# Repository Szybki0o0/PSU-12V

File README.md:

# Dual Power Supply Circuit

## Overview
This schematic represents a **dual power supply circuit** that converts **12V AC** input into **regulated ±12V DC output**. It uses **linear voltage regulators (7812 and 7912)** to provide stable positive and negative 12V outputs.

## Main Components
1. **Power Input:**
   - **J1 (Barrel Jack Connector)**: Accepts **12V AC** input.
   - **D1, D2 (1N4007 Diodes)**: Forms a **bridge rectifier** for AC-to-DC conversion.

2. **Filtering Section:**
   - **C1, C2, C3, C4, C5, C6 (4700µF capacitors)**: Large **electrolytic capacitors** used for smoothing rectified DC voltage.
   - **C7, C8, C9, C10 (1µF capacitors)**: Additional filtering for improved stability.

3. **Voltage Regulators:**
   - **U1 (7812 Voltage Regulator)**: Provides a regulated **+12V DC output**.
   - **U2 (7912 Voltage Regulator)**: Provides a regulated **-12V DC output**.

4. **Protection Components:**
   - **D3 (1N4007 Diode)**: Protection diode to prevent reverse polarity damage.

## How It Works
1. **AC to DC Conversion**  
   - The **12V AC input** is rectified using **D1 and D2**, converting AC voltage to **pulsating DC**.
   - The **large electrolytic capacitors (C1-C6)** smooth the voltage to **reduce ripple**.

2. **Voltage Regulation**  
   - The **7812 regulator (U1)** outputs a steady **+12V DC**.
   - The **7912 regulator (U2)** outputs a steady **-12V DC**.
   - Small capacitors (C7-C10) help improve transient response and further reduce noise.

3. **Output**  
   - The final output at the **VoltageOut** terminal provides **+12V, GND, and -12V**, suitable for powering **operational amplifiers, audio circuits, and other dual-supply electronics**.

## Psysical implementation
Project has't been implemented on PCB but tested on a breadboard.

## Possible Improvements
- Adding **heat sinks** to the **7812 and 7912** for better thermal management. (It's mandatory)
- Using **fast-recovery diodes (e.g., UF4007)** instead of **1N4007** to improve efficiency.
- Implementing a **fuse** at the input for added protection.

## Applications
- **Operational amplifier circuits**
- **Audio amplifier power supplies**
- **Analog signal processing systems**
- **Dual-rail power supply requirements**

## Author
Jakub Konior

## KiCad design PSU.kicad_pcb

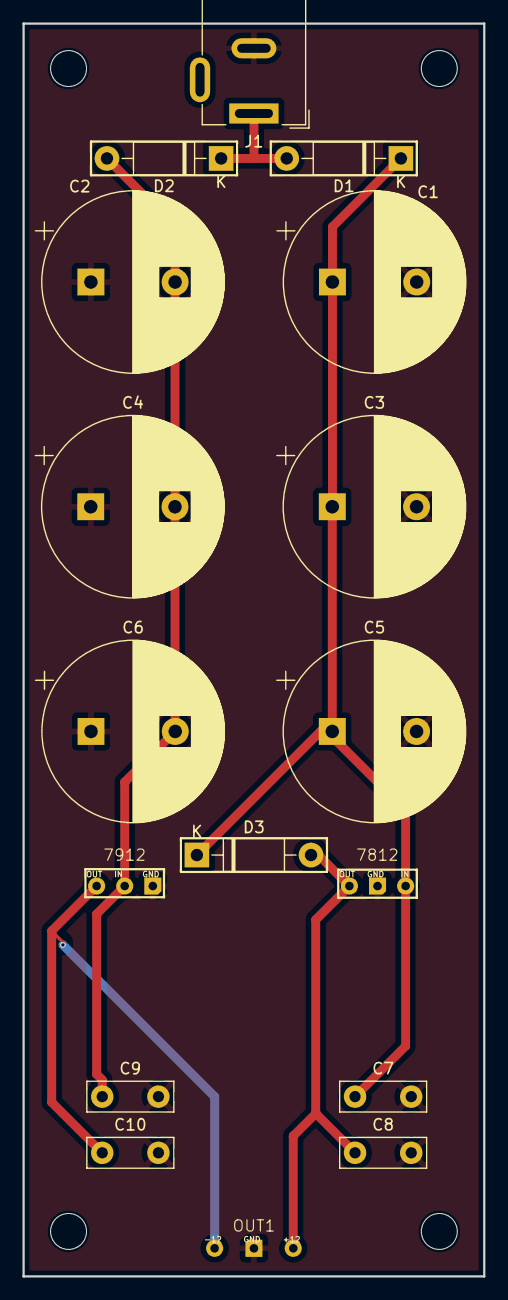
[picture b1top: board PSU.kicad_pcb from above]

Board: 2 copper layers, 41.0 x 111.5 mm, 17 parts (0 on the bottom side), 6 nets.

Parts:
7812: L7812
7912: L7912
C1, C2, C3, C4, C5, C6: 4700uF; CP_Radial_D16.0mm_P7.50mm
C7, C8, C9, C10: 1uF; C_Disc_D7.5mm_W2.5mm_P5.00mm
D1, D2, D3: 1N4007; D_DO-41_SOD81_P10.16mm_Horizontal
J1: Barrel_Jack_Switch_Pin3Ring; BarrelJack_Wuerth_6941xx301002
OUT1: OUT+-12V

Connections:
12VAC: D1.2 (A), D2.1 (K), J1.1
GND: 7812.2 (GND), 7912.1 (GND), C1.2, C2.1, C3.2, C4.1, C5.2, C6.1, C7.2, C8.2, C9.2, C10.2, J1.2, OUT1.2 (GND)
unnamed: 7812.1 (IN), C1.1, C3.1, C5.1, C7.1, D1.1 (K), D3.1 (K)
unnamed: 7912.2 (VI), C2.2, C4.2, C6.2, C9.1, D2.2 (A)
unnamed: 7812.3 (OUT), C8.1, D3.2 (A), OUT1.3 (+12V)
unnamed: 7912.3 (VO), C10.1, OUT1.1 (-12V)

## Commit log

2025-02-19 Upload of project files
